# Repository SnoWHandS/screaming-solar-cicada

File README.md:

# Screaming Solar Cicada

A sun-fed, MCU-free noise bug that trickle-charges from a tiny **Anysolar KXOB** “SolarBIT” module, then screams in bursts when the storage node crosses a “battery good” threshold—then goes quiet until the cap refills. No code, no sleep states—just **PV → boost → cap → hysteresis → load switch → discrete astable → magnetic buzzer.**

---

## How it works (signal chain)

### 1. Harvest (KXOB)

The main energy source is a compact monocrystalline **KXOB** module—for example **KXOB25-04X3F** / **-TR** class (~22 × 7 mm, ~2 V MPP neighborhood, ~10–15 mA-scale current under decent light).

- The panel feeds `VIN_DC` through a **BAT54-class Schottky** (polarity, forward drop, and saner behavior when the charger isn’t drawing).
- **Stringing:** This design targets **1S** (one module) so `VIN_DC` stays inside the **BQ25505** window. **2S** only if you prove worst-case open-circuit never violates `VIN_DC` limits (**~5.1 V** recommended, **5.5 V** abs max). **Parallel** modules are fine for more charging current in weak light.

### 2. PMIC

**TI BQ25505** — **22 µH** boost from `VIN_DC` ↔ `LBOOST`; cold-start from **~600 mV** typical at the input (after the diode, plan margin), then normal operation down to very low `VIN` once running.

**MPPT** uses a high-impedance divider on `VOC_SAMP` from `VIN_DC` so the chip tracks a fraction of the panel’s open-circuit voltage (KXOB **V<sub>OC</sub>** is usually **~2–3 V** class depending on SKU and illumination).

### 3. Storage and thresholds

Energy stacks on the storage / `VSTOR`–`VBAT_*` network. The main reservoir is a large electrolytic (**1000 µF / 6.3 V** on the tank in `crktboi`).

| Function | Programming |
|----------|-------------|
| **`VBAT_OV`** | Two-resistor divider from `VRDIV` — build uses **~6.8 MΩ + 6.2 MΩ** (~**13 MΩ** total class). |
| **`VBAT_OK`** | Three-resistor string (**~5.1 MΩ + 5.11 MΩ + 5.11 MΩ** class) — rising vs falling “turn load on/off” vs **`VBIAS` ≈ 1.21 V**. |

Sanity-check **`VBAT_OV` ≥ `VBAT_OK` rising threshold** per TI ordering rules; divider pin mapping matters.

### 4. Load switch

`VBAT_OK` drives **2N7002** → **AO3401A** high-side: **`Vstore` → `+3V0`** to the audio section. When the tank sags past the low trip, `+3V0` collapses and the chirp ends.

### 5. Noise

**BC847** astable — **~174 kΩ** + **1 nF** timing (**~4 kHz** ballpark), **~1 kΩ** collectors. **GSC1102YB-3V4000** buzzer does the actual scream.

#### Oscillator Design

The discrete astable multivibrator is built around a pair of BC847 NPN transistors. The selected RC timing values (`174 kΩ` and `1 nF`) tune the oscillation frequency to approximately 4 kHz, which closely matches the resonant frequency of the magnetic buzzer to produce the loudest possible chirp.

*Schematic of the oscillator circuit.*

*Frequency response showing the ~4 kHz operating point.*

---

## Early direction (not the hero)

The first concept used **arrays of VBPW34S photodiodes** (**3S×3P** strings, per-string Schottkys, picky light economics). That stays interesting as a stunt, but this description treats it as **initial exploration** — the **KXOB** is the practical, repeatable harvester you’d actually leave on a windowsill.

---

## Repo / CAD

**KiCad** project **`crktboi`**:

- **`power`** sheet — KXOB / `VIN_DC`, BQ25505, load switch  
- **`oscillator`** sheet — astable + buzzer  

**ERC** and **Highlight net** are the real documentation.

---

## Expectations

- **Chirp cadence** — charge rate from the KXOB in your real light vs load current when the PFET is on — scale like **Δ*t* ~ *C*·Δ*V* / *I*<sub>load</sub>**.
- **Louder / longer** — more µF or lower mean buzzer current.
- **More frequent chirps** — more mW from the cell or a tighter OK window (trade noise against TI threshold constraints).

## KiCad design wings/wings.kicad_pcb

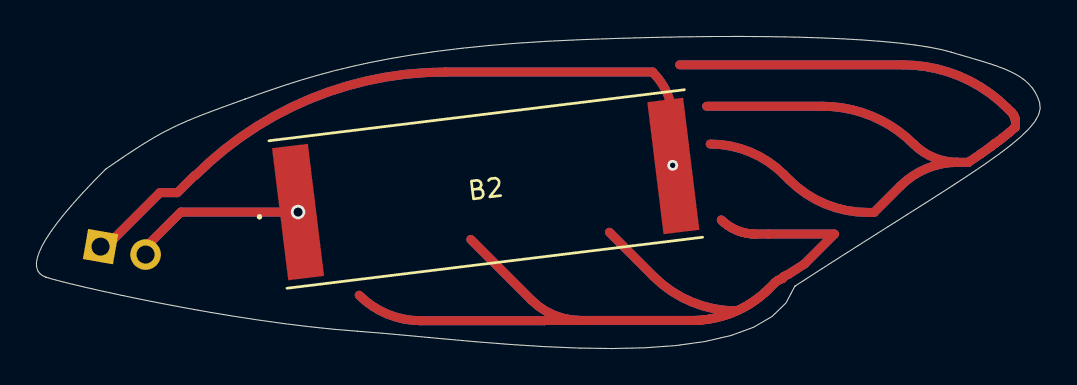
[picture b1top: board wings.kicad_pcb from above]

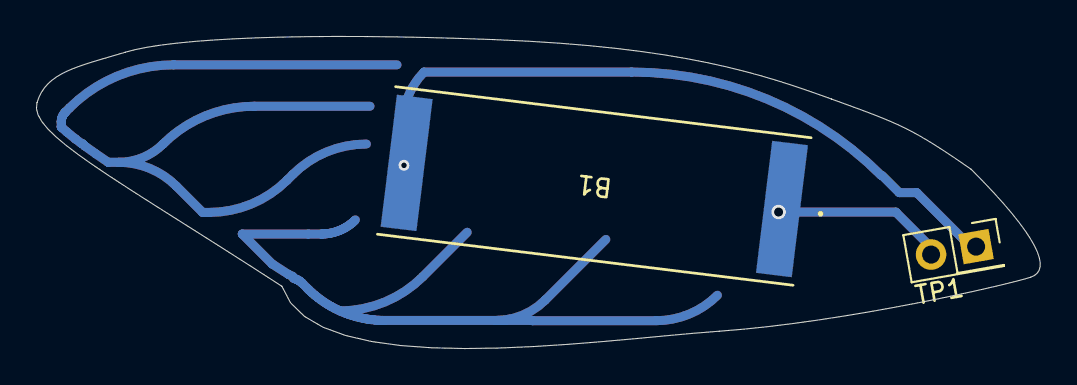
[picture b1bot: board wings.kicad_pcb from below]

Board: 2 copper layers, 55.8 x 17.3 mm, 3 parts (2 on the bottom side), 2 nets.

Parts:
B1, B2: KXOB25-03X4F-TB; KXOB25_AAR
TP1: TestPoint_2Pole; PinSocket_2x01_P2.54mm_Vertical

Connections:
unnamed: B1.1, B2.1, TP1.2
unnamed: B1.2, B2.2, TP1.1

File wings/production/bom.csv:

Designator,Footprint,Quantity,Value,LCSC Part #
"B1, B2",KXOB25_AAR,2,KXOB25-03X4F-TB,
TP1,PinSocket_2x01_P2.54mm_Vertical,1,TestPoint_2Pole,C492401

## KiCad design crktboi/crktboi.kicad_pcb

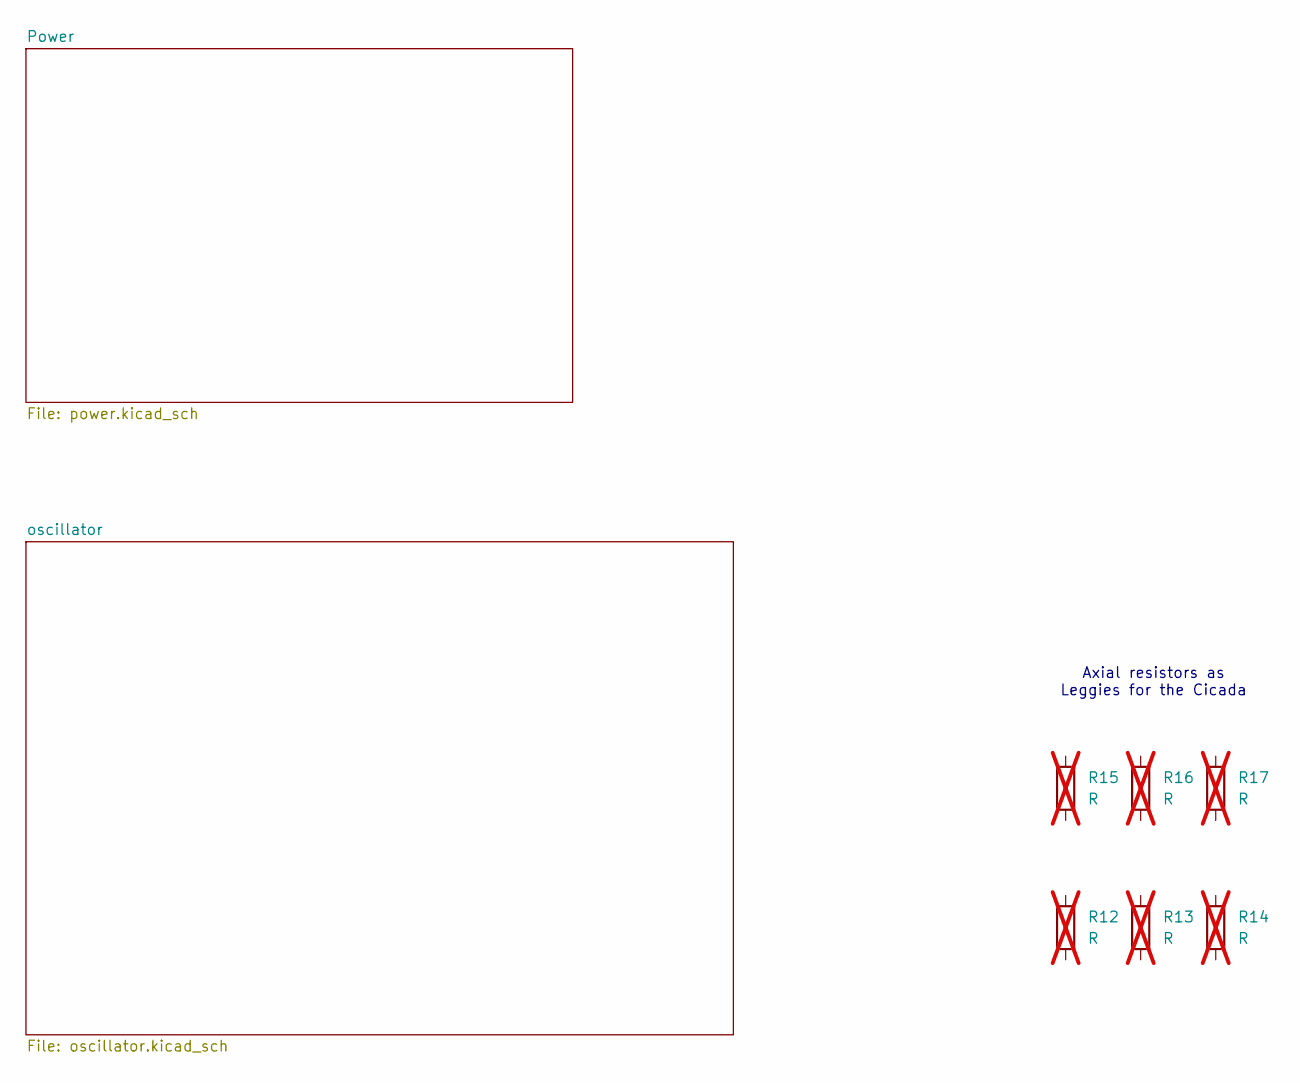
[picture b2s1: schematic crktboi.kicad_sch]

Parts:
R12, R13, R14, R15, R16, R17: R; R_Axial_DIN0204_L3.6mm_D1.6mm_P5.08mm_Horizontal; not fitted

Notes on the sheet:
Axial resistors as Leggies for the Cicada

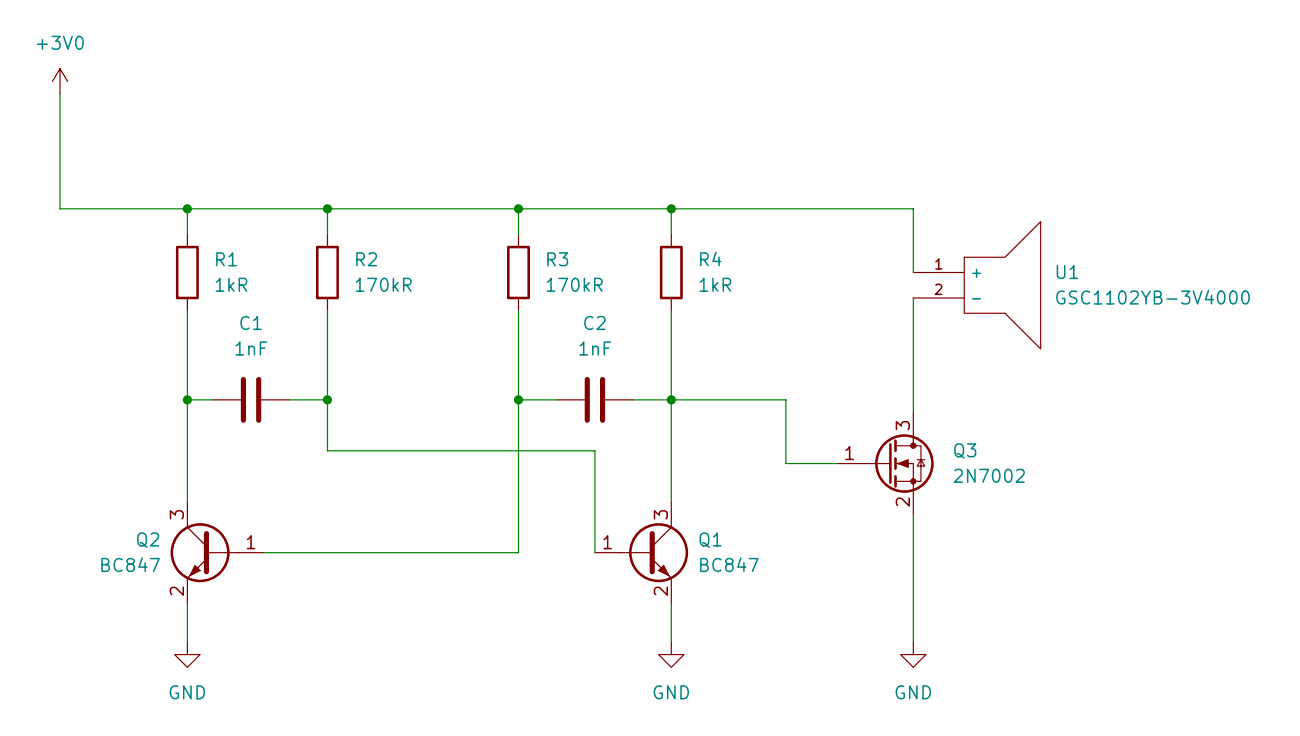
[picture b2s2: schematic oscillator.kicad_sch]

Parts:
C1, C2: 1nF; C_0603_1608Metric_Pad1.08x0.95mm_HandSolder; LCSC C100040
Q1, Q2: BC847; SOT-23; LCSC C2138
Q3: 2N7002; SOT-23; LCSC C8545
R1, R4: 1kR; R_0603_1608Metric_Pad0.98x0.95mm_HandSolder; LCSC C22548
R2, R3: 170kR; R_0603_1608Metric_Pad0.98x0.95mm_HandSolder; LCSC C22890
U1: GSC1102YB-3V4000; BUZ-SMD_L11.0-W9.0; LCSC C255332

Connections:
+3V0: R1.1, R2.1, R3.1, R4.1, U1.1 (+); also elsewhere on the board
GND: Q1.2 (E), Q2.2 (E), Q3.2 (S); also elsewhere on the board
unnamed: C1.2, Q1.1 (B), R2.2
unnamed: C2.2, Q1.3 (C), Q3.1 (G), R4.2
unnamed: C2.1, Q2.1 (B), R3.2
unnamed: C1.1, Q2.3 (C), R1.2
unnamed: Q3.3 (D), U1.2 (-)

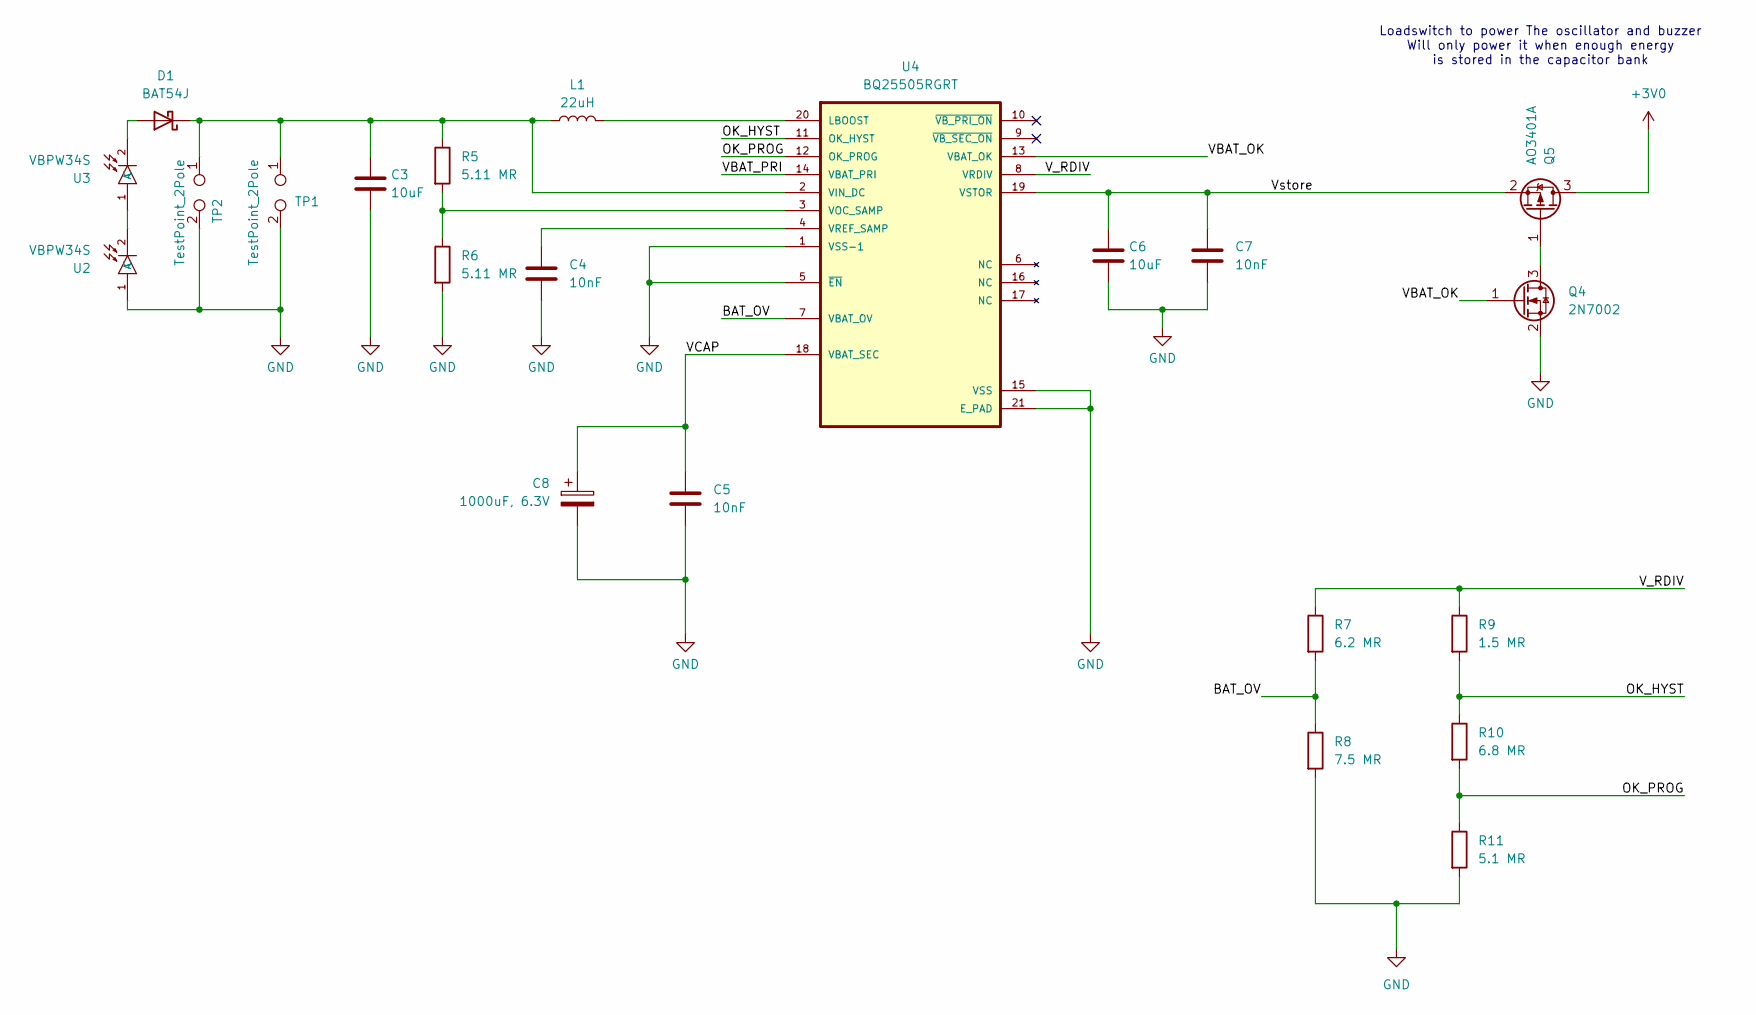
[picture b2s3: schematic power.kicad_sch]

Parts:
C3, C6: 10uF; C_0805_2012Metric; PARTNO CL21A106KOQNNNG; LCSC C307520
C4, C5, C7: 10nF; C_0402_1005Metric; PARTNO CC0402KRX7R8BB103; LCSC C327025
C8: 1000uF, 6.3V; CP_Elec_8x10; LCSC C49256842
D1: BAT54J; D_SOD-323F; LCSC C130415
L1: 22uH; L_0805_2012Metric; PARTNO MLZ2012N220LT000; LCSC C383411
Q4: 2N7002; SOT-23; LCSC C8545
Q5: AO3401A; SOT-23; LCSC C15127
R5, R6: 5.11 MR; R_0402_1005Metric; PARTNO RC0402FR-075M11L; LCSC C477744
R7: 6.2 MR; R_0402_1005Metric; PARTNO RM04J625CT; LCSC C477768
R8: 7.5 MR; R_0402_1005Metric; PARTNO RC0402FR-077M5L; LCSC C327241
R9: 1.5 MR; R_0402_1005Metric; PARTNO RK73H1ETTP1504F; LCSC C138034
R10: 6.8 MR; R_0402_1005Metric; PARTNO CRCW04026M80FKED; LCSC C477775
R11: 5.1 MR; R_0402_1005Metric; PARTNO RK73H1ETTP5104F; LCSC C477747
TP1, TP2: TestPoint_2Pole; PinSocket_2x01_P2.54mm_Vertical; LCSC C492401
U2, U3: VBPW34S; SENSOR-SMD_L4.4-W3.9; LCSC C145262
U4: BQ25505RGRT; QFN50P350X350X100-21N-D; PARTNO BQ25505RGRT; LCSC C2876730

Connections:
+3V0: Q5.3 (D); also elsewhere on the board
/Power/BAT_OV: R7.2, R8.1, U4.7 (VBAT_OV)
/Power/OK_HYST: R9.2, R10.1, U4.11 (OK_HYST)
/Power/OK_PROG: R10.2, R11.1, U4.12 (OK_PROG)
/Power/VBAT_OK: Q4.1 (G), U4.13 (VBAT_OK)
/Power/VBAT_PRI: U4.14 (VBAT_PRI)
/Power/VCAP: C5.1, C8.1, U4.18 (VBAT_SEC)
/Power/V_RDIV: R7.1, R9.1, U4.8 (VRDIV)
/Power/Vstore: C6.1, C7.1, Q5.2 (S), U4.19 (VSTOR)
GND: C3.2, C4.2, C5.2, C6.2, C7.2, C8.2, Q4.2 (S), R6.2, R8.2, R11.2, TP1.2, TP2.2, U2.1 (A), U4.1 (VSS-1), U4.5 (~EN), U4.15 (VSS), U4.21 (E_PAD); also elsewhere on the board
unnamed: D1.2 (A), U3.2 (C)
unnamed: Q4.3 (D), Q5.1 (G)
unnamed: U2.2 (C), U3.1 (A)
unnamed: L1.2, U4.20 (LBOOST)
unnamed: R5.2, R6.1, U4.3 (VOC_SAMP)
unnamed: C4.1, U4.4 (VREF_SAMP)

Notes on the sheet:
Loadswitch to power The oscillator and buzzer Will only power it when enough energy is stored in the capacitor bank

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
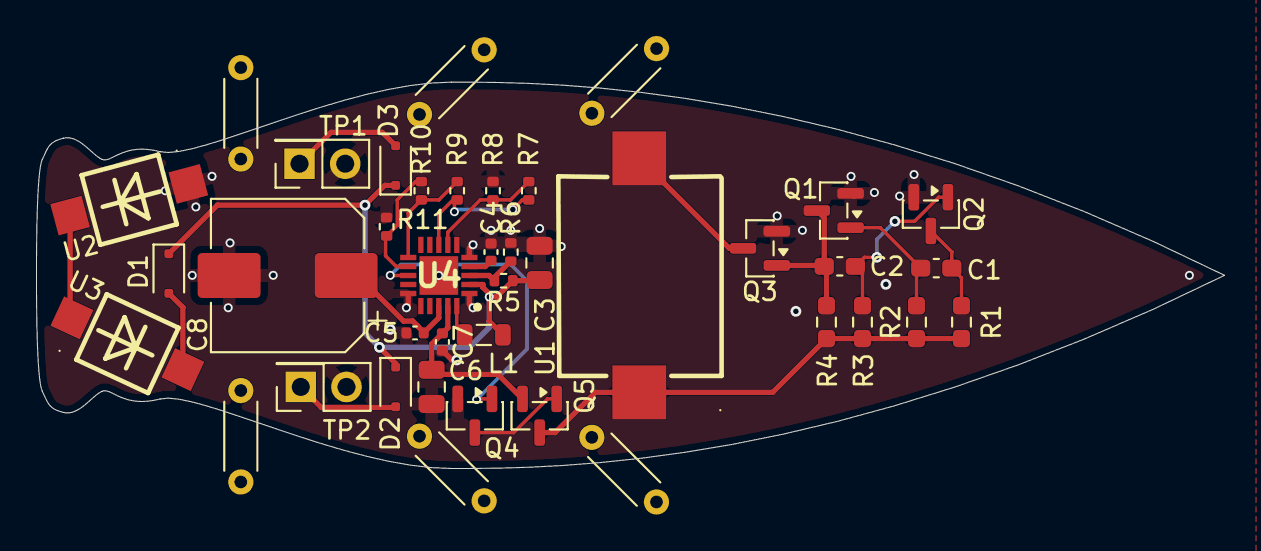
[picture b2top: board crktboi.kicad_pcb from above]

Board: 2 copper layers, 66.0 x 21.5 mm, 40 parts (0 on the bottom side), 23 nets.

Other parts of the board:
D2, D3: BAT54J; D_SOD-323F

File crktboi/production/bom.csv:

Designator,Footprint,Quantity,Value,LCSC Part #
"C1, C2",0603,2,1nF,C100040
"C3, C6",0805,2,10uF,C307520
"C4, C5, C7",0402,3,10nF,C327025
C8,CP_Elec_8x10,1,"1000uF, 6.3V",C49256842
D1,D_SOD-323F,1,BAT54J,
L1,0805,1,22uH,C383411
"Q1, Q2",SOT-23,2,BC847,C2138
"Q3, Q4",SOT-23,2,2N7002,C8545
Q5,SOT-23,1,AO3401A,C15127
"R1, R4",0603,2,1kR,C22548
R10,0402,1,6.8 MR,C477775
R11,0402,1,5.1 MR,C477747
"R12, R13, R14, R15, R16, R17",R_Axial_DIN0204_L3.6mm_D1.6mm_P5.08mm_Horizontal,6,R,
"R2, R3",0603,2,170kR,C22890
"R5, R6",0402,2,5.11 MR,C477744
R7,0402,1,6.2 MR,C477768
R8,0402,1,7.5 MR,C327241
R9,0402,1,1.5 MR,C138034
"TP1, TP2",PinSocket_2x01_P2.54mm_Vertical,2,TestPoint_2Pole,C492401
U1,BUZ-SMD_L11.0-W9.0,1,GSC1102YB-3V4000,C255332
"U2, U3",SENSOR-SMD_L4.4-W3.9,2,VBPW34S,C145262
U4,QFN50P350X350X100-21N-D,1,BQ25505RGRT,C2876730

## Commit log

2026-04-11 gitignore
2026-04-11 wednesday session resources
2026-04-11 Added library for GSC1102YB-3V4000 buzzer
2026-04-11 oscill schem
2026-04-11 fix things
2026-04-11 new proj that might work
2026-04-11 lil pcb
2026-04-11 Made some progress on the BQ25505 in the old schematic. Will polish it off and import into new project next.
2026-04-16 Added the power circuit to the design and considered VBAT_OK as the power control output for the design. Still todo is reducing capacitor bank size and adjusting BQ25505 parameters
2026-04-16 Removed history
2026-04-18 Added a plan document & updated design with tweaks for 3S3P photodiodes
2026-04-18 Updated PCB layout with all parts I think we need for power.
2026-04-18 Added LCSC part numbers to each part in the schematic
2026-04-19 Changed the shape to be a bit more like a cicada. Added 3D models to parts missing their assignment
2026-04-19 Added photodiodes to the base design for eyes on the cicada.
2026-04-19 Added resistors as legs for the cicada and updated LCSC part numbers for new parts
2026-04-19 Completed the board layout and ran through the DRC. Adjusted clearance limits to make it work
2026-04-19 Created fabrication files and added back csv files from the gitignore
2026-04-19 Created a wing project and tried to get the outline of a wing. Having issues with board outline overlap when importing outlines from pictures online
2026-04-20 big panel, new wing
2026-04-21 Added BAT54J diodes to the input connectors of the PV headers
2026-04-21 Added a graphic to the back of the base board of a Cicada
2026-04-21 removed the cicada graphic a it was too busy
2026-04-21 tracks for wings
2026-04-21 rotated terminals
2026-04-21 dryfit
2026-04-21 Created 3D models of main body board, wings and double sided wings. added 3D models for solar cells
2026-04-21 Created gerbers of Wing and 3D renders of the assembly for docs
2026-04-21 Updated Gerbers of new body PCB
2026-04-21 Changed wings to 0.24mm thick FPC and re-rendered
2026-04-22 Add header for Cicada Boi in README
    readme
2026-04-22 Added project description
2026-04-22 Renamed everything from jmny cricket to cicada
2026-04-22 Updated readme with a breakdown of the projects operation
2026-04-22 Added images to the readme with a descirptor of the oscillator
